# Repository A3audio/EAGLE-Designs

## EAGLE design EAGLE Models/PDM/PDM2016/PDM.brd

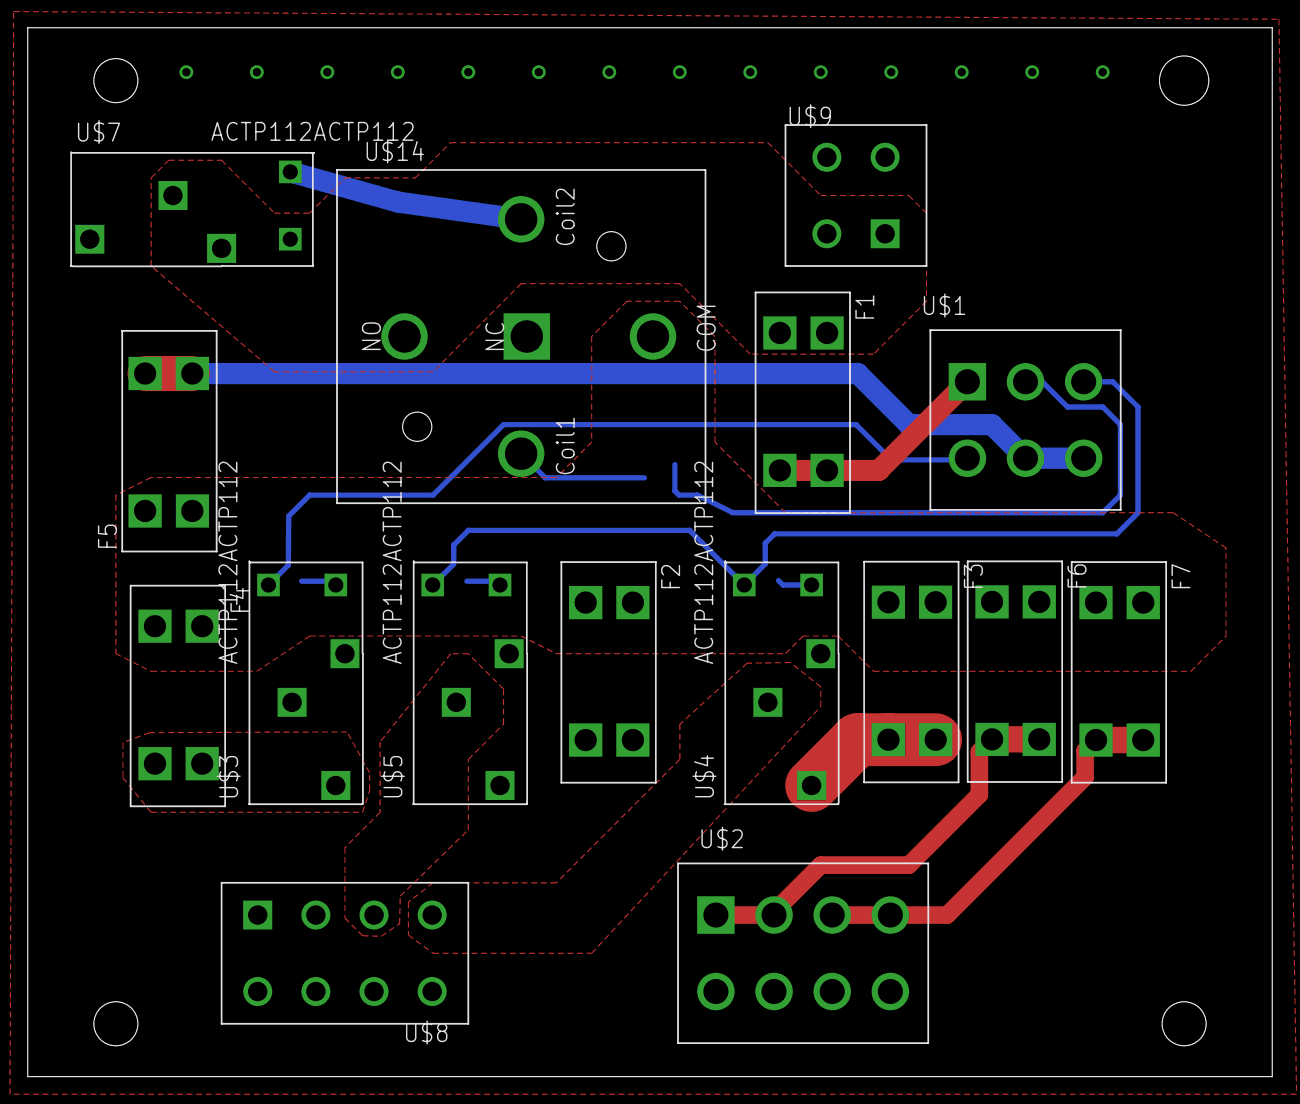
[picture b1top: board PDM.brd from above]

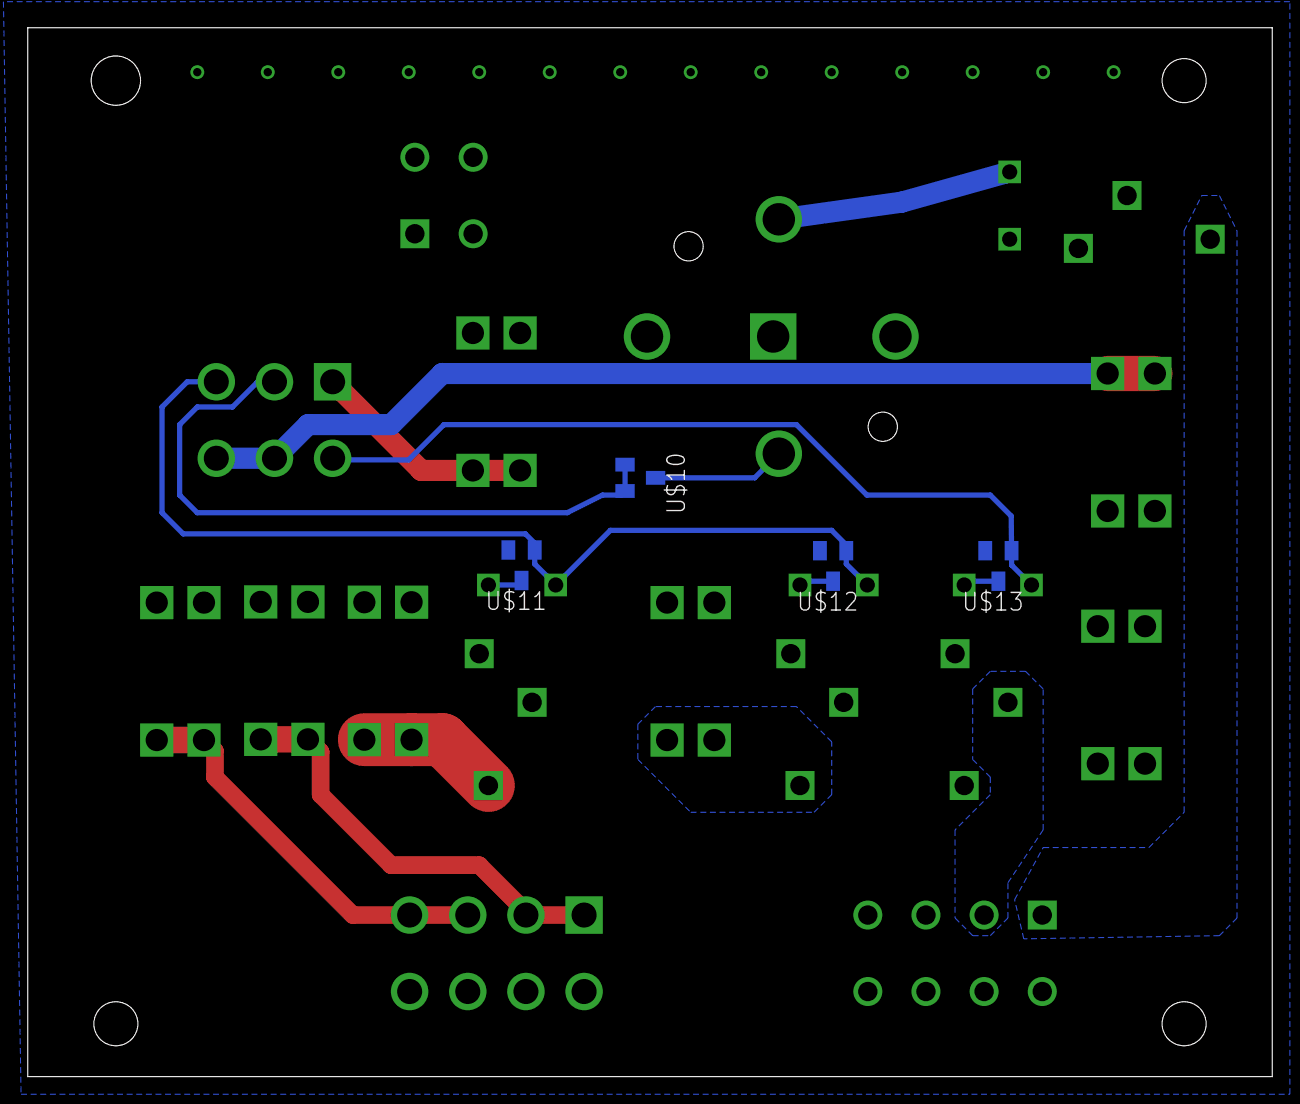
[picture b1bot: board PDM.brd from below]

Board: 2 copper layers, 89.7 x 75.6 mm, 20 parts (4 on the bottom side), 19 nets.

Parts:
F1, F2, F3, F4, F5, F6, F7: 3568
U$1: 1586041-6
U$2: 1586042-8
U$3, U$4, U$5, U$7: ACTP112ACTP112; ACTP112
U$8: 15-97-7084
U$9: 15-97-8043
U$10, U$11, U$12, U$13: MMBD4448H-7-F; SOT23-3
U$14: VCF4-1000

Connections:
12V: F2.1, F2.2, F3.1, F3.2, F4.1, F4.2, F5.1, F5.2, F6.1, F6.2, F7.1, F7.2, U$3.COIL2, U$4.COIL2, U$5.COIL2, U$11.3, U$12.3, U$13.3, U$14.COM
12V_DAQ_OUT: F6.3, F6.4, U$2.1, U$2.2
12V_FUSED_ECU: F7.3, F7.4, U$2.3, U$2.4
12V_SHIFT_OUT: F5.3, F5.4, U$1.5, U$1.6
A23: U$1.4, U$3.COIL1, U$13.1
A24: U$1.3, U$4.COIL1, U$5.COIL1, U$11.1, U$12.1
BAT_12V: F1.1, F1.2, U$7.NO, U$9.1, U$9.2, U$14.NO
BAT_+12_FUSED: F1.3, F1.4, U$1.1
CHARGE_SIG: U$7.COIL1, U$14.COIL2
FAN: U$3.NO, U$8.2
FAN_12V: F4.3, F4.4, U$3.COM
FUEL: U$5.NO, U$8.3
FUEL_12V: F2.3, F2.4, U$5.COM
GND: U$2.5, U$2.6, U$2.7, U$2.8, U$7.COIL2, U$8.5, U$8.6, U$8.7, U$8.8, U$9.3, U$9.4
IGNITION: U$4.NO, U$8.4
IGN_12V: F3.3, F3.4, U$4.COM
KILL_SWITCH_DIODE: U$10.3, U$14.COIL1
KILL_SWT: U$1.2, U$10.1
RECTIFIER: U$7.COM, U$8.1

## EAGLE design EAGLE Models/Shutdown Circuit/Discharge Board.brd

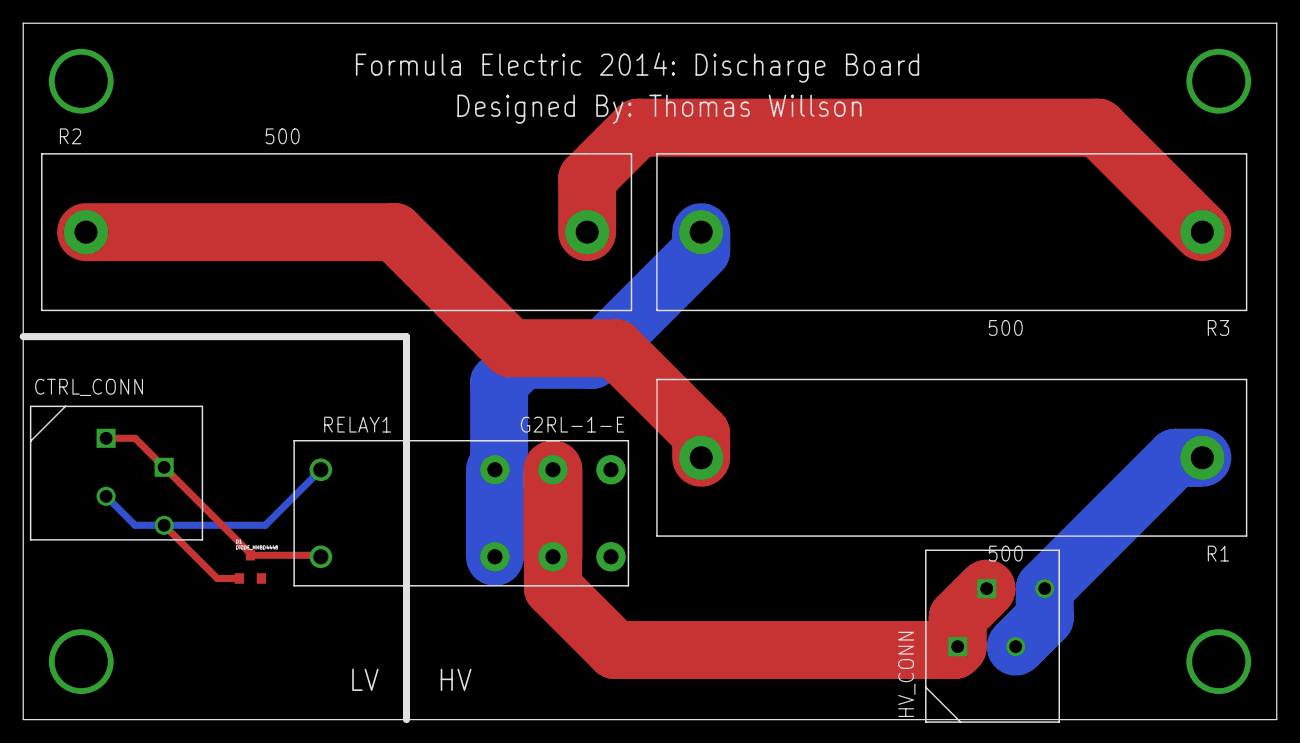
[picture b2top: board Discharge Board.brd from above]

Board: 2 copper layers, 108.0 x 60.0 mm, 7 parts (0 on the bottom side), 7 nets.

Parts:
CTRL_CONN: CONN_2; CONNECTOR_2
D1: DIODE_MMBD4448; SOT-23-3
HV_CONN: CONN_2; CONNECTOR_2
R1, R2, R3: 500; VISHAY_FS20W_RES
RELAY1: G2RL-1-E; G2RL-1-E_RELAY

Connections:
GND: CTRL_CONN.3, CTRL_CONN.4, D1.P$2, RELAY1.P$8
unnamed: R3.P$2, RELAY1.P$2, RELAY1.P$7
unnamed: HV_CONN.1, HV_CONN.2, RELAY1.P$3, RELAY1.P$6
unnamed: HV_CONN.3, HV_CONN.4, R1.P$1
unnamed: R1.P$2, R2.P$1
unnamed: R2.P$2, R3.P$1
TSMS_IN: CTRL_CONN.1, CTRL_CONN.2, D1.P$1, RELAY1.P$1

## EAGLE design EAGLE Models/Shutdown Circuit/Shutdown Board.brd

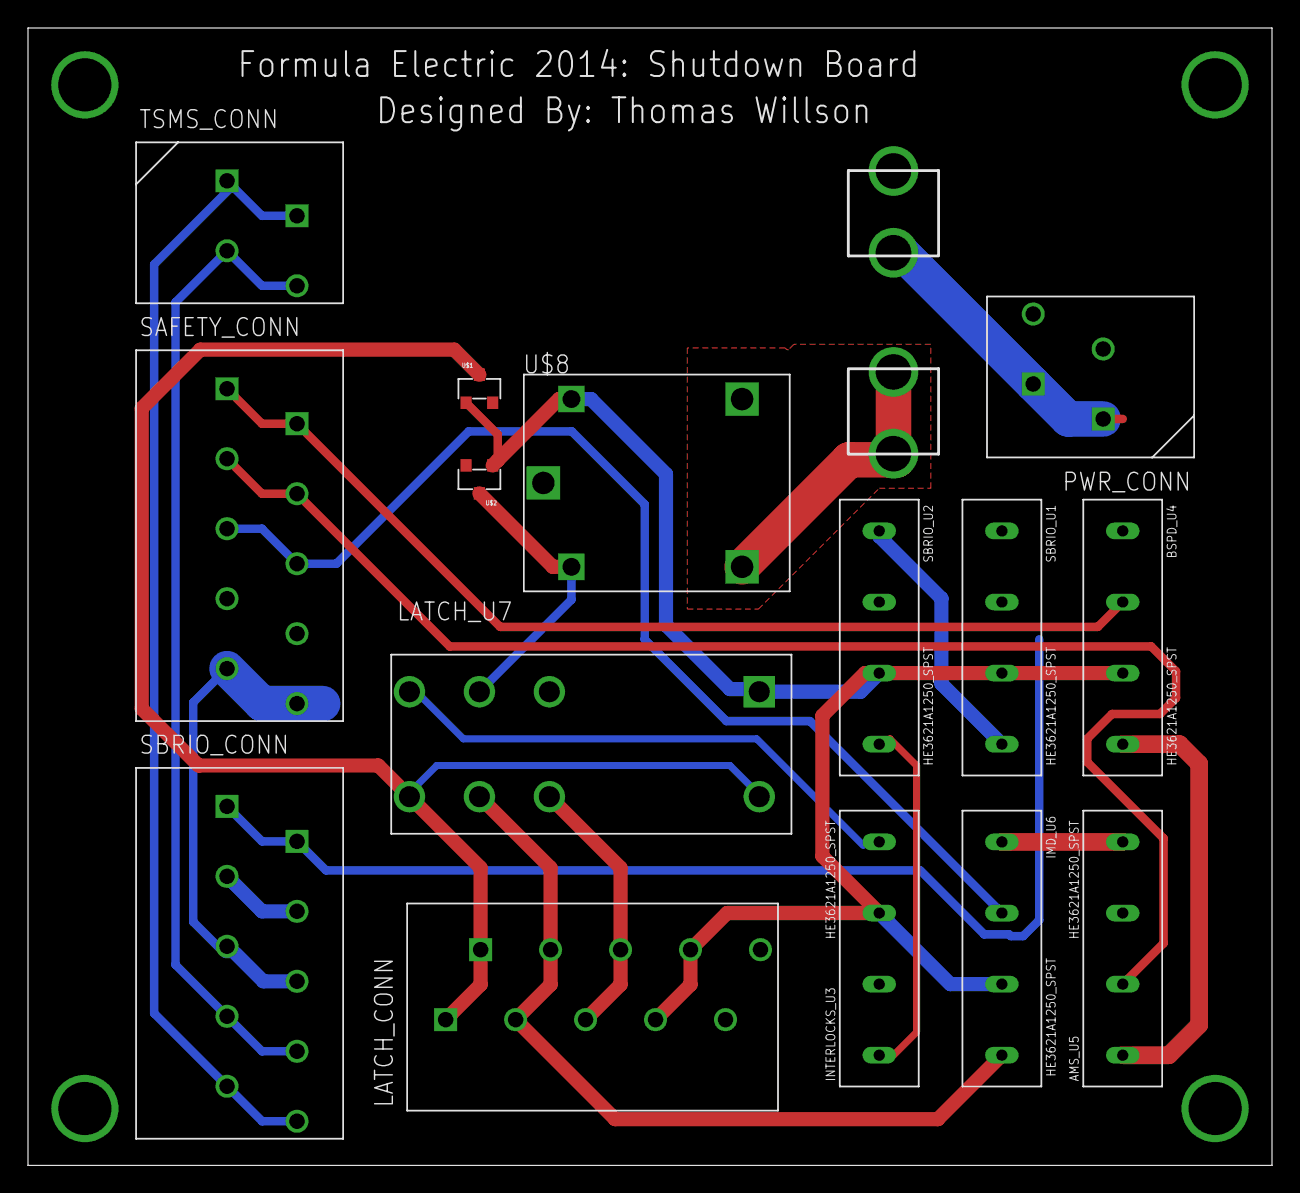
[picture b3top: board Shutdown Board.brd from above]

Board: 2 copper layers, 88.9 x 81.3 mm, 16 parts (0 on the bottom side), 21 nets.

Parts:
AMS_U5: HE3621A1250_SPST
BSPD_U4: HE3621A1250_SPST
F1: FUSEX20MM; FUSE_5MM
IMD_U6: HE3621A1250_SPST
INTERLOCKS_U3: HE3621A1250_SPST
LATCH_CONN: CONN_5; CONNECTOR_5
LATCH_U7: JW2SN-DC12V; DPDT_JW2_FORM_C
PWR_CONN: CONN_2; CONNECTOR_2
SAFETY_CONN: CONN_5; CONNECTOR_5
SBRIO_CONN: CONN_5; CONNECTOR_5
SBRIO_U1, SBRIO_U2: HE3621A1250_SPST
TSMS_CONN: CONN_2; CONNECTOR_2
U$1, U$2: DIODE_MMBD4448; SOT-23-3
U$8: RELAY

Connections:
AMS_OK-: AMS_U5.C+, SAFETY_CONN.3, SAFETY_CONN.4
BSPD_OK+: BSPD_U4.C+, SAFETY_CONN.1, SAFETY_CONN.2
GLV+: AMS_U5.C-, BSPD_U4.S1, F1.3, F1.4, PWR_CONN.1, PWR_CONN.2, SBRIO_U1.S1
GND: BSPD_U4.C-, IMD_U6.C-, INTERLOCKS_U3.C-, LATCH_CONN.7, LATCH_CONN.8, LATCH_U7.COIL_1, PWR_CONN.3, PWR_CONN.4, SBRIO_U1.C-, SBRIO_U2.C-, U$1.P$2, U$2.P$2, U$8.V1
IMD_OK+: IMD_U6.C+, SAFETY_CONN.5, SAFETY_CONN.6
INTER_OK+: INTERLOCKS_U3.C+, SAFETY_CONN.7, SAFETY_CONN.8
LATCH_LED+: LATCH_CONN.5, LATCH_CONN.6, LATCH_U7.NC_2
LATCH_SW_IN: LATCH_CONN.1, LATCH_CONN.2, LATCH_U7.COIL_2, LATCH_U7.NO_2, U$1.P$1
LATCH_SW_OUT: IMD_U6.S2, LATCH_CONN.3, LATCH_CONN.4, LATCH_U7.CENTER_2
unnamed: SBRIO_U1.S2, SBRIO_U2.S1
unnamed: INTERLOCKS_U3.S1, SBRIO_U2.S2
unnamed: AMS_U5.S1, BSPD_U4.S2
unnamed: AMS_U5.S2, IMD_U6.S1
unnamed: F1.1, F1.2, U$8.A
PRECHARGE_DONE+: SBRIO_CONN.7, SBRIO_CONN.8, TSMS_CONN.3, TSMS_CONN.4
SBRIO_OK+_1: SBRIO_CONN.1, SBRIO_CONN.2, SBRIO_U1.C+
SBRIO_OK+_2: SBRIO_CONN.3, SBRIO_CONN.4, SBRIO_U2.C+
SHUTDOWN_OK+: INTERLOCKS_U3.S2, LATCH_U7.NO_1
TSMS_IN+: SBRIO_CONN.9, SBRIO_CONN.10, TSMS_CONN.1, TSMS_CONN.2
TSMS_OUT+: SAFETY_CONN.9, SAFETY_CONN.10, SBRIO_CONN.5, SBRIO_CONN.6, U$8.CENTER
TSMS_OUT_CTRL+: LATCH_U7.CENTER_1, U$2.P$1, U$8.V2

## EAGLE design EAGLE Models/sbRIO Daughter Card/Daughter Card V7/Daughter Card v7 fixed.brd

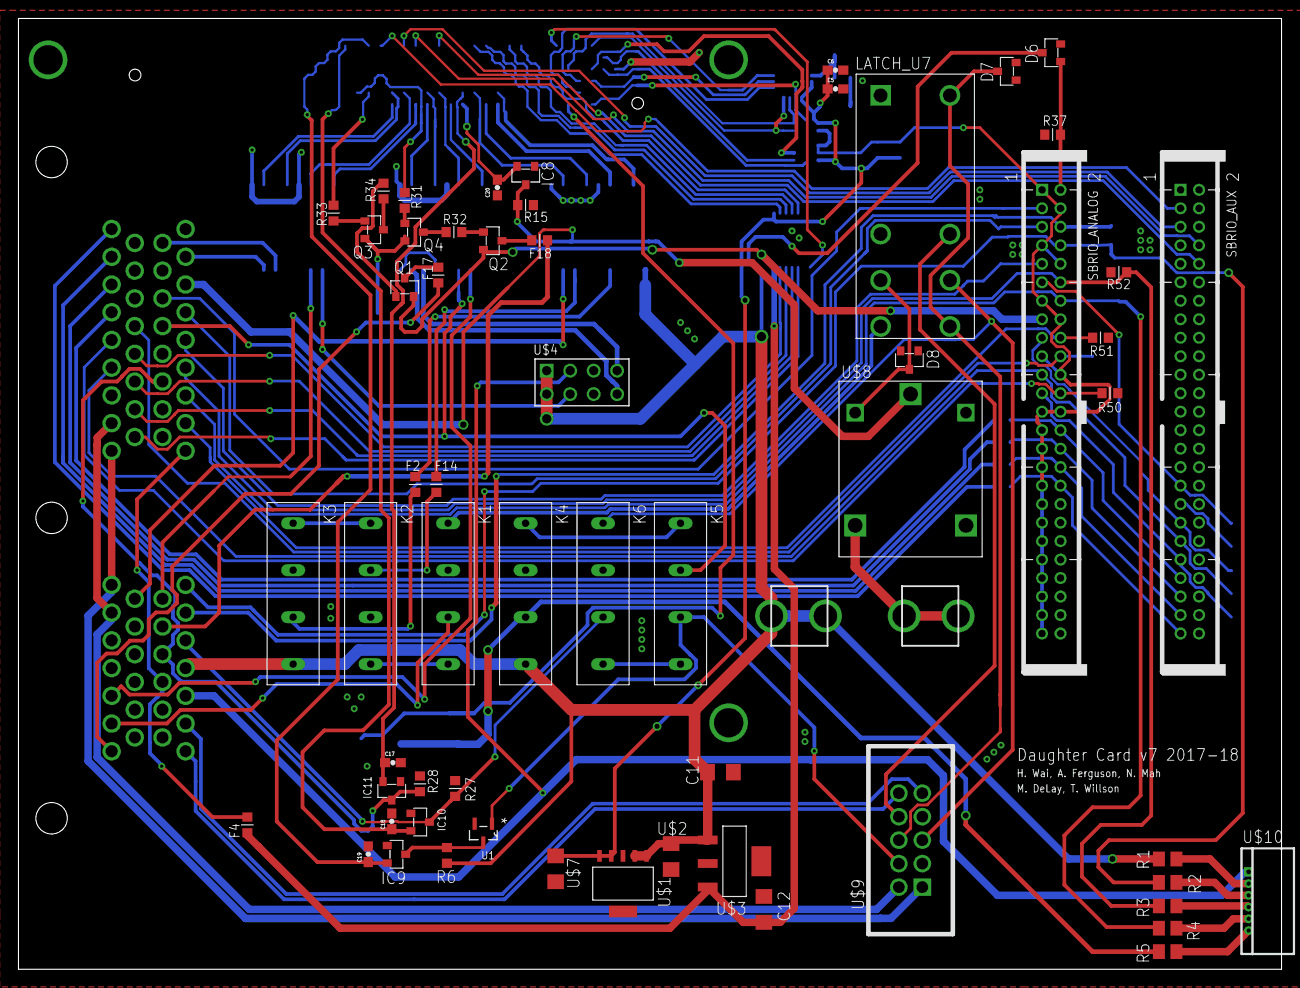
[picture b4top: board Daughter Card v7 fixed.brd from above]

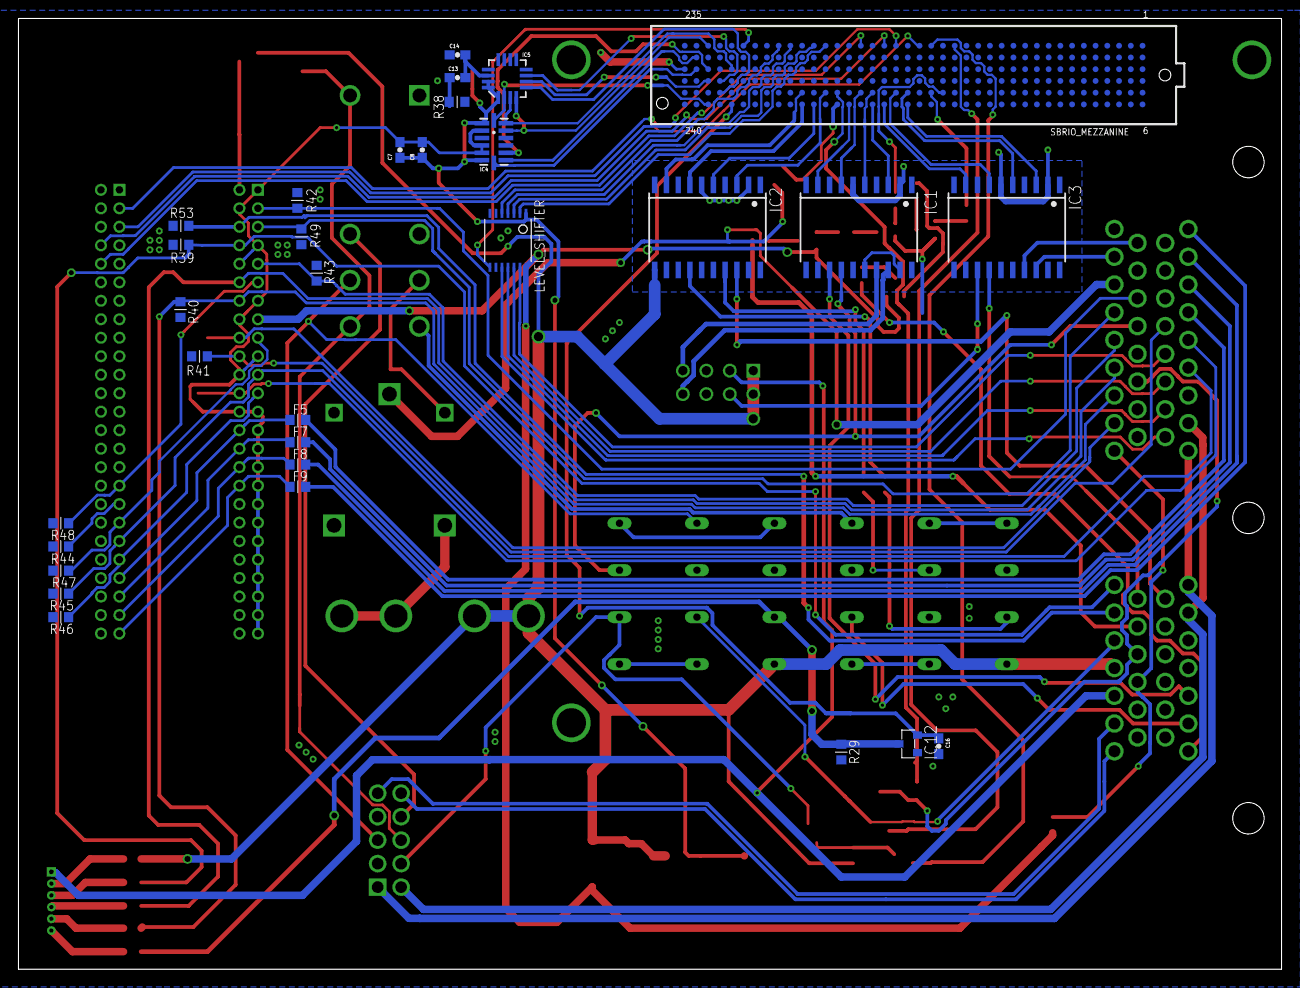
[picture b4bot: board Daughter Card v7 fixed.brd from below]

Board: 2 copper layers, 136.7 x 102.9 mm, 92 parts (31 on the bottom side), 123 nets.

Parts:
C5, C7: .1uF; 0603-CAP
C6: 10uF; 0603-CAP
C8, C16, C17, C18, C19, C20: 1uF; 0603-CAP
C11: 0.1uF; C1206
C12: 0.22uF; C1206
C13: 470nF; 0603-CAP
C14: 10nF; 0603-CAP
D6: MMBZ5238B-7-F; SOT-23-3
D7, D8: DIODE_MMBD4448; SOT-23-3
F2, F14: 250mA; R0603
F3: FUSEX20MM; FUSE_5MM
F4: 0.5A PTC; R0603
F5, F7, F8, F9: 10mA PTC; R0603
F17, F18: 1A PTC; R0603
IC1, IC2, IC3: BTS716G; PG-DSO-20
IC4: ADXL345; LGA14
IC5: L3G4200D; LGA16-4X4
IC8, IC9, IC10, IC11, IC12: MIC5225-3.3YM5-TR; SOT-23-3
K1, K2, K3, K4, K5, K6: HE3621A1250_SPST
LATCH_U7: JW2SN-DC12V; DPDT_JW2_FORM_C
LEVEL_SHIFTER: TSSOP14
Q1, Q2: MMBT4403-7-F; SOT-23-3
Q3, Q4: MMBT4401-7-F; SOT-23-3
R1, R2, R3, R4, R5: 0; M0805
R6: 100K; R0603
R15, R27, R28, R29, R37, R38: 10K; R0603
R31, R32, R33, R34: 4.7K; R0603
R39, R40, R41, R42, R43, R44, R45, R46, R47, R48, R49, R50, R51, R52, R53: 100k; R0603
SBRIO_ANALOG: SBRIO_MIO; SBRIO_J502_J503
SBRIO_AUX: SBRIO_AUX; SBRIO_J502_J503
SBRIO_MEZZANINE: SBRIO_RMC; SEAM-40-XX.X-XX-06-X-A
U1: DMN3404L-7; SOT95P235X112-3N
U$1: TPS7A4533
U$2, U$7: 10uF; C1206
U$3: LM340MP-5.0; SOT-223-4
U$4: HARWIN_M20-9980445
U$6: SUPERSEAL1.0_60POS
U$8: RELAY
U$9: SBRIO_BMS_CONN; SBRIO_W
U$10: SULLINS_1MM_6P_HEADER; SULLINS_1MM_HEADER

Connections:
3.3V: C5.1, C6.1, C7.1, C8.1, IC4.1, IC4.6, IC5.1, IC5.15, IC5.16, LEVEL_SHIFTER.1, U$1.P$4, U$1.P$5, U$7.1
5V: C12.1, F4.1, LEVEL_SHIFTER.14, Q1.P$3, Q2.P$3, SBRIO_ANALOG.P$15, U$3.3
5V_FUSED: F4.2, U$6.A9, U$6.B11
5V_IO_1: F17.1, U$6.B26
12V: C11.1, D6.P$1, F3.3, F3.4, IC1.1, IC1.10, IC1.11, IC1.12, IC1.15, IC1.16, IC1.19, IC1.20, IC2.1, IC2.10, IC2.11, IC2.12, IC2.15, IC2.16, IC2.19, IC2.20, IC3.1, IC3.10, IC3.11, IC3.12, IC3.15, IC3.16, IC3.19, IC3.20, K3.S1, K4.S1, R1.2, R6.1, U$1.P$1, U$1.P$2, U$2.1, U$3.1, U$4.P1, U$4.P5, U$6.B4
ACCUMULATOR_FANS: IC1.18, U$4.P8
AI7: R50.2, SBRIO_ANALOG.P$24, U$6.A30
AI8: R42.1, SBRIO_ANALOG.P$3, U$6.A12
AI9: R49.2, SBRIO_ANALOG.P$5, U$6.A4
AI10: R43.1, SBRIO_ANALOG.P$9, U$6.A5
AI11: R48.2, SBRIO_ANALOG.P$11, SBRIO_AUX.P$33
AI12: R44.1, SBRIO_AUX.P$35
AI13: R47.2, SBRIO_ANALOG.P$17, SBRIO_AUX.P$37
AI15: R46.2, SBRIO_ANALOG.P$23, SBRIO_AUX.P$41
AMS_OK-: K5.C-, U1.1, U$9.P$4
AO0: F5.1, SBRIO_ANALOG.P$28, SBRIO_AUX.P$43
AO1: F7.1, SBRIO_ANALOG.P$30, SBRIO_AUX.P$45
AO2: F8.1, SBRIO_ANALOG.P$32, SBRIO_AUX.P$47
AO3: F9.1, SBRIO_ANALOG.P$34, SBRIO_AUX.P$49
BMS_CAN_H: U$6.B7, U$9.P$10
BMS_CAN_L: U$6.B6, U$9.P$9
BRAKELIGHT: IC3.17, U$6.A10
BRAKE_PRESS_IN_1: R3.2, R52.2, SBRIO_ANALOG.P$12, U$6.A6
BRAKE_PRESS_IN_2: R4.2, R40.1, SBRIO_ANALOG.P$14, U$6.A7
BSPD_OK+: IC12.P$1, K4.C+, R5.2, R29.1
BUZZER_OUT: IC3.18, U$6.A2
CAN_H: U$6.A33, U$6.B21, U$9.P$2
CAN_L: U$6.A34, U$6.B20, U$9.P$1
COOLANT_PUMP: IC1.17, U$4.P4
DC_DC_DISABLE: F18.1, U$6.B9
DIO0: IC4.14, IC5.2, SBRIO_MEZZANINE.228
DIO1: C16.1, IC12.P$3, SBRIO_MEZZANINE.216
DIO5: IC2.7, SBRIO_MEZZANINE.180
DIO6: IC2.5, SBRIO_MEZZANINE.174
DIO7: C20.1, IC8.P$3, SBRIO_MEZZANINE.162
DIO8: IC1.9, SBRIO_MEZZANINE.156
DIO9: IC1.3, SBRIO_MEZZANINE.144
DIO10: IC3.9, SBRIO_MEZZANINE.138
DIO11: IC3.3, SBRIO_MEZZANINE.126
DIO16: IC4.7, SBRIO_MEZZANINE.231
DIO17: IC4.9, SBRIO_MEZZANINE.225
DIO18: IC4.13, IC5.3, SBRIO_MEZZANINE.213
DIO32: IC5.5, SBRIO_MEZZANINE.221
DIO37: IC2.9, SBRIO_MEZZANINE.179
DIO38: IC2.3, SBRIO_MEZZANINE.167
DIO39: C17.1, IC11.P$3, SBRIO_MEZZANINE.161
DIO40: IC1.7, SBRIO_MEZZANINE.149
DIO41: IC1.5, SBRIO_MEZZANINE.143
DIO42: IC3.7, SBRIO_MEZZANINE.131
DIO43: IC3.5, SBRIO_MEZZANINE.125
DIO44: R33.1, SBRIO_MEZZANINE.113
DIO45: R31.1, SBRIO_MEZZANINE.107
DIO48: IC4.8, SBRIO_MEZZANINE.230
DIO64: IC5.6, SBRIO_MEZZANINE.226
DIO65: IC5.7, SBRIO_MEZZANINE.220
DIO81: IC4.12, IC5.4, SBRIO_MEZZANINE.223
DIO83: LEVEL_SHIFTER.8, SBRIO_MEZZANINE.205
DIO85: LEVEL_SHIFTER.5, SBRIO_MEZZANINE.187
DIO86: LEVEL_SHIFTER.4, SBRIO_MEZZANINE.181
DIO87: LEVEL_SHIFTER.3, SBRIO_MEZZANINE.169
DIO88: LEVEL_SHIFTER.2, SBRIO_MEZZANINE.163
DIO90: SBRIO_AUX.P$10, SBRIO_MEZZANINE.145
DIO91: SBRIO_AUX.P$8, SBRIO_MEZZANINE.133
DIO92: SBRIO_AUX.P$5, SBRIO_MEZZANINE.127
DIO93: SBRIO_AUX.P$3, SBRIO_MEZZANINE.115
DIO94: C19.1, IC9.P$3, SBRIO_MEZZANINE.109
DIO95: C18.1, IC10.P$3, SBRIO_MEZZANINE.97
DIO_GND: C7.2, C8.2, IC4.2, IC4.4, IC4.5, SBRIO_ANALOG.P$1, SBRIO_ANALOG.P$4, SBRIO_ANALOG.P$7, SBRIO_ANALOG.P$10, SBRIO_ANALOG.P$13, SBRIO_ANALOG.P$16, SBRIO_ANALOG.P$19, SBRIO_ANALOG.P$22, SBRIO_ANALOG.P$25, SBRIO_ANALOG.P$26, SBRIO_ANALOG.P$27, SBRIO_ANALOG.P$29, SBRIO_ANALOG.P$31, SBRIO_ANALOG.P$33, SBRIO_ANALOG.P$35, SBRIO_ANALOG.P$37, SBRIO_ANALOG.P$39, SBRIO_ANALOG.P$41, SBRIO_ANALOG.P$43, SBRIO_ANALOG.P$45, SBRIO_ANALOG.P$47, SBRIO_ANALOG.P$49
FAN_PWM_OUT: IC3.13, U$4.P6
GND: C5.2, C6.2, C11.2, C12.2, C14.1, C16.2, C17.2, C18.2, C19.2, C20.2, D7.P$2, D8.P$2, IC1.2, IC1.6, IC2.2, IC2.6, IC3.2, IC3.6, IC5.8, IC5.9, IC5.10, IC5.11, IC5.12, IC5.13, IC8.P$2, IC9.P$2, IC10.P$2, IC11.P$2, IC12.P$2, K1.C-, K2.C-, K3.C-, K4.C-, K6.C-, LATCH_U7.COIL_1, LEVEL_SHIFTER.7, Q3.P$3, Q4.P$3, R15.2, R27.2, R28.2, R29.2, R37.1, R38.2, R39.2, R40.2, R41.2, R42.2, R43.2, R44.2, R45.2, R46.1, R47.1, R48.1, R49.1, R50.1, R51.1, R52.1, R53.1, SBRIO_AUX.P$7, SBRIO_AUX.P$9, SBRIO_AUX.P$11, SBRIO_AUX.P$13, SBRIO_AUX.P$15, SBRIO_AUX.P$17, SBRIO_AUX.P$18, SBRIO_AUX.P$19, SBRIO_AUX.P$20, SBRIO_AUX.P$21, SBRIO_AUX.P$22, SBRIO_AUX.P$23, SBRIO_AUX.P$24, SBRIO_AUX.P$25, SBRIO_AUX.P$26, SBRIO_AUX.P$27, SBRIO_AUX.P$28, SBRIO_AUX.P$29, SBRIO_AUX.P$30, SBRIO_AUX.P$31, SBRIO_AUX.P$32, SBRIO_AUX.P$34, SBRIO_AUX.P$36, SBRIO_AUX.P$38, SBRIO_AUX.P$40, SBRIO_AUX.P$42, SBRIO_AUX.P$44, SBRIO_AUX.P$46, SBRIO_AUX.P$48, SBRIO_AUX.P$50, SBRIO_MEZZANINE.237, U1.2, U$1.P$3, U$1.P$6, U$2.2, U$3.2, U$3.4, U$4.P3, U$4.P7, U$6.A1, U$6.A11, U$6.A14, U$6.A16, U$6.A17, U$6.A18, U$6.A19, U$6.A20, U$6.A32, U$6.B12, U$6.B13, U$6.B15, U$6.B16, U$6.B17, U$6.B18, U$6.B19, U$6.B22, U$6.B23, U$7.2, U$8.V1, U$9.P$7
HIGH_CURRENT_IN: R2.2, R39.1, SBRIO_ANALOG.P$8, U$6.B1
IMD_OK+: IC10.P$1, K6.C+, R27.1, U$6.B3
INTER_OK+: K1.C+, U$6.B25
K4: K4.S2, K5.S1
LATCH_LED+: LATCH_U7.NC_2, U$9.P$8
LATCH_SW_IN: D7.P$1, LATCH_U7.COIL_2, LATCH_U7.NO_2, U$9.P$6
LATCH_SW_OUT: K6.S2, LATCH_U7.CENTER_2, U$9.P$5
LOW_CURRENT_IN: R53.2, SBRIO_ANALOG.P$6, U$6.B2
unnamed: K2.S1, K3.S2
unnamed: F5.2, U$6.A29
unnamed: D6.P$2, R37.2, SBRIO_ANALOG.P$2
unnamed: Q1.P$2, R34.2
unnamed: F7.2, U$6.A28
unnamed: K1.S1, K2.S2
unnamed: Q3.P$1, R34.1
unnamed: F8.2, U$6.A27
unnamed: F9.2, U$6.A26
unnamed: C13.1, R38.1
unnamed: R1.1, U$10.P2
unnamed: K5.S2, K6.S1
unnamed: F3.1, F3.2, U$8.A
unnamed: R2.1, U$10.P3
unnamed: R3.1, U$10.P4
unnamed: R4.1, U$10.P5
unnamed: Q4.P$1, R32.1
unnamed: Q4.P$2, R31.2
unnamed: R5.1, U$10.P6
unnamed: Q3.P$2, R33.2
unnamed: IC9.P$1, R6.2, U1.3
unnamed: C13.2, C14.2, IC5.14
unnamed: F17.2, Q1.P$1
unnamed: F18.2, Q2.P$1
unnamed: Q2.P$2, R32.2
PO3: IC1.14, K5.C+, U$6.A13
POSITIVE_AIR_ENABLE: IC3.14, U$6.B8
PRECHARGE_DONE+: IC1.13, U$6.B24
SBRIO_OK+_1: F2.1, IC2.14
SBRIO_OK+_1_RELAY_IN: F2.2, K3.C+
SBRIO_OK+_2: F14.1, IC2.17
SBRIO_OK_2_RELAY: F14.2, K2.C+
SHUTDOWN_OK+: K1.S2, LATCH_U7.NO_1
SIGNAL_GND: U$4.P2, U$6.B5, U$10.P1
STEERING_POS: R45.1, SBRIO_ANALOG.P$21, SBRIO_AUX.P$39, U$6.A31
THROTTLE_IN_1: R51.2, SBRIO_ANALOG.P$18, U$6.A8
THROTTLE_IN_2: R41.1, SBRIO_ANALOG.P$20, U$6.A21
THROTTLE_OK_OUT: IC2.18, U$6.B14
TSMS_IN+: IC11.P$1, R28.1, U$6.A15, U$6.B10
TSMS_OUT+: IC8.P$1, R15.1, U$6.A3, U$8.CENTER
TSMS_OUT_CTRL+: D8.P$1, LATCH_U7.CENTER_1, U$8.V2
WS1: LEVEL_SHIFTER.13, U$6.A22
WS2: LEVEL_SHIFTER.12, U$6.A23
WS3: LEVEL_SHIFTER.11, U$6.A24
WS4: LEVEL_SHIFTER.10, U$6.A25

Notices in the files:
parts and their libraries:
SparkFun-Passives: Licensing: CC v3.0 Share-Alike You are welcome to use this library for commercial purposes.
